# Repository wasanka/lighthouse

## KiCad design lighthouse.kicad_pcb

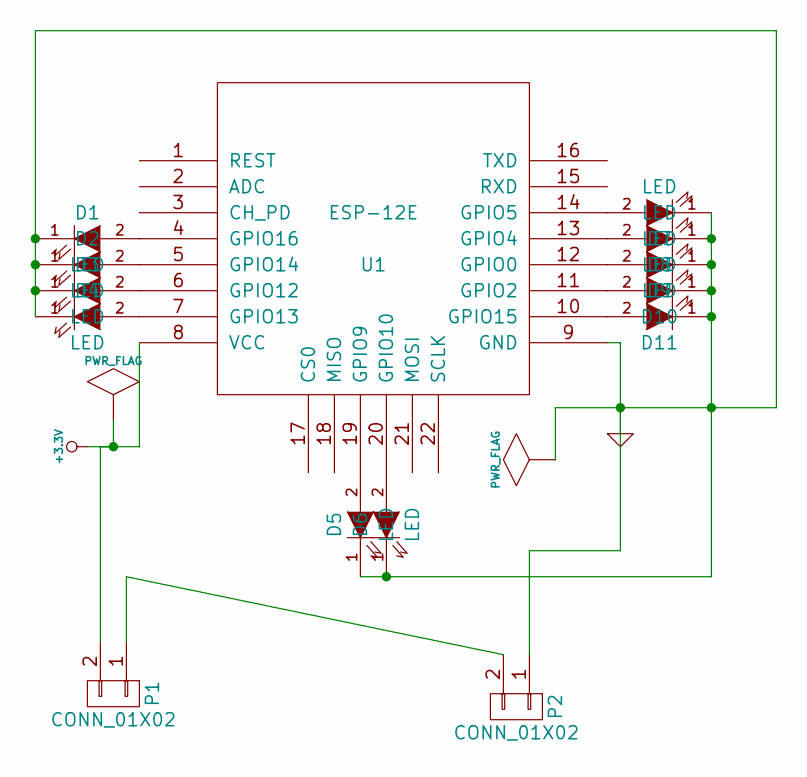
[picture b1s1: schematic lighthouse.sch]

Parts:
D1, D2, D3, D4, D5, D6, D7, D8, D9, D10, D11: LED; LED-5MM
P1, P2: CONN_01X02; Pin_Header_Straight_1x02
U1: ESP-12E

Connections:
+3.3V: P1.2, U1.8 (VCC)
GND: D1.1 (K), D2.1 (K), D3.1 (K), D4.1 (K), D5.1 (K), D6.1 (K), D7.1 (K), D8.1 (K), D9.1 (K), D10.1 (K), D11.1 (K), P2.1, U1.9 (GND)
unnamed: D1.2 (A), U1.4 (GPIO16)
unnamed: D2.2 (A), U1.5 (GPIO14)
unnamed: D3.2 (A), U1.6 (GPIO12)
unnamed: D4.2 (A), U1.7 (GPIO13)
unnamed: D5.2 (A), U1.19 (GPIO9)
unnamed: D6.2 (A), U1.20 (GPIO10)
unnamed: D7.2 (A), U1.14 (GPIO5)
unnamed: D8.2 (A), U1.13 (GPIO4)
unnamed: D9.2 (A), U1.12 (GPIO0)
unnamed: D10.2 (A), U1.11 (GPIO2)
unnamed: D11.2 (A), U1.10 (GPIO15)
unnamed: P1.1, P2.2

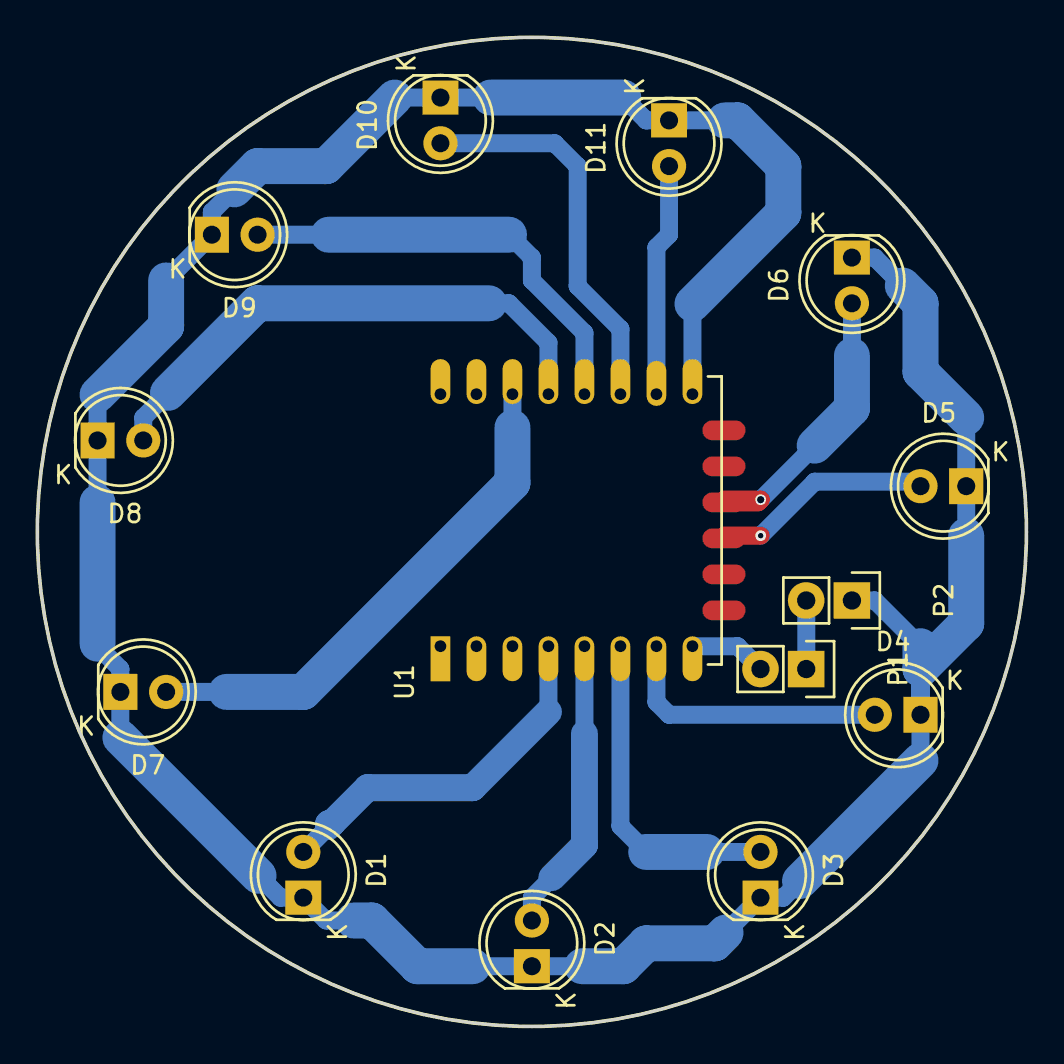
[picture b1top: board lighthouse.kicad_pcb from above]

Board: 2 copper layers, 54.9 x 54.9 mm, 14 parts (0 on the bottom side), 14 nets.
